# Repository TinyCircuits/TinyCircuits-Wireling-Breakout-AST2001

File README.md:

# TinyCircuits 0.1" Breakout Wireling AST2001

The design files are located under design_files/ for the TinyCircuits AST2001 Rev 1 PCB. This is a Wireling board which is the smallest our line has to offer, used for making other analog or I2C hardware components usable in the Wireling format.
Format is in Cadsoft Eagle format - Eagle version 6.2 was used for the original design.

For more infomation on this, check out the product page at TinyCircuits.com

# License:

Design by TinyCircuits.
All design files are released under the Creative Commons Attribution Share-Alike 3.0 License, see the following link for details: http://creativecommons.org/licenses/by-sa/3.0

All text above must be included in any redistribution or derived design

This project uses designs and concepts developed as part of the Arduino project and the LilyPad project.  The TinyCircuits design files themselves (schematics, PCB and libraries) are not directly derived from these works' design files and have been created new, however the concepts and basic architecture behind the TinyDuino and TinyLily products are derived and we thank the hard work of the organizations below for their contributions to open-source hardware:
  
Original Arduino Uno Design by Team Arduino

LilyPad Arduino Design by Leah Buechley and Sparkfun Electronics

Please support the open-source hardware community

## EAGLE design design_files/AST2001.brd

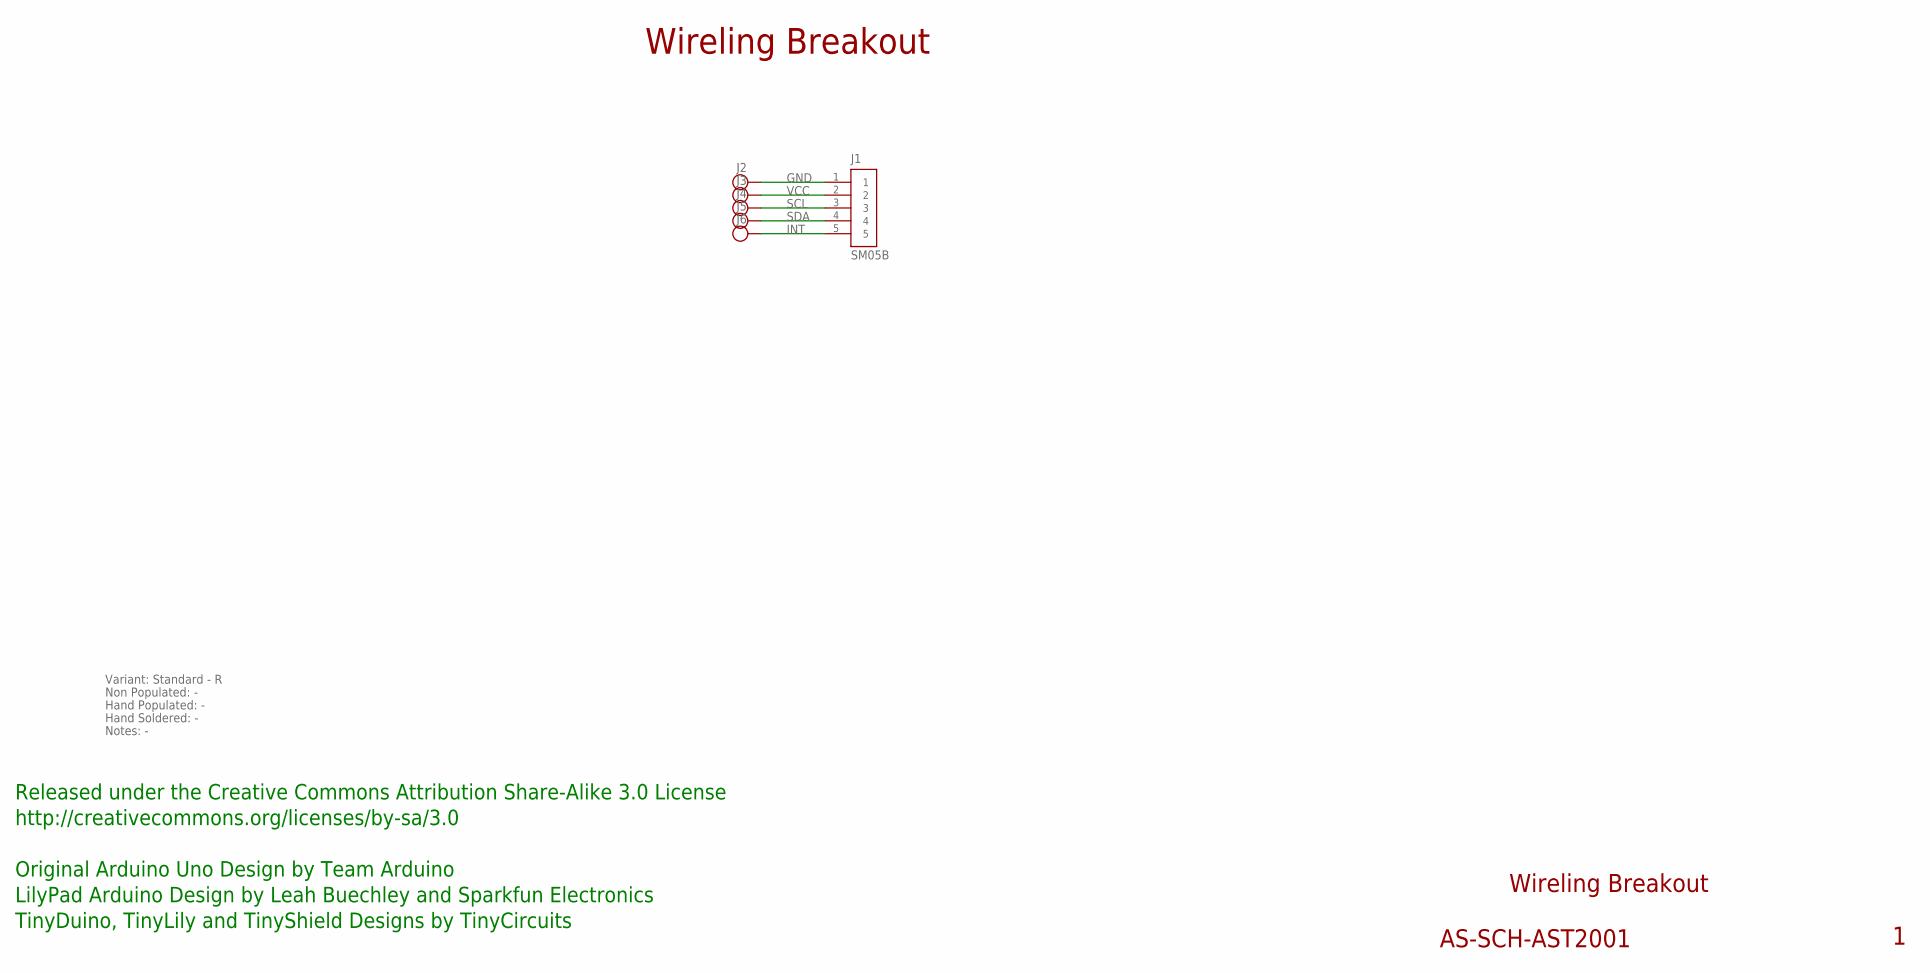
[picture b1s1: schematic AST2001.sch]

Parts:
J1: SM05B; JST_SH_5X1_EDGE
J2, J3, J4, J5, J6: PIN_1X.1"1; 1X.1"_2

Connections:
GND: J1.1, J2.1
INT: J1.5, J6.1
SCL: J1.3, J4.1
SDA: J1.4, J5.1
VCC: J1.2, J3.1

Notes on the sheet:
Wireling Breakout
AS-SCH-AST2001
Released under the Creative Commons Attribution Share-Alike 3.0 License
http://creativecommons.org/licenses/by-sa/3.0
Original Arduino Uno Design by Team Arduino
TinyDuino, TinyLily and TinyShield Designs by TinyCircuits
LilyPad Arduino Design by Leah Buechley and Sparkfun Electronics
Variant: Standard - R
Non Populated: -
Hand Populated: -
Hand Soldered: -
Notes: -

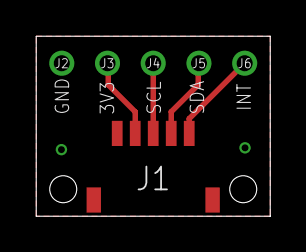
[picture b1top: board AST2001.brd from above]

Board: 2 copper layers, 13.0 x 10.0 mm, 7 parts (0 on the bottom side), 5 nets.

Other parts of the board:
U$1: DOCFIELD-TINYCIRCUITS-PCB

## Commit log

2019-12-17 updated documentation
2020-04-21 Programs & picutres
2020-08-14 Add CAD data
